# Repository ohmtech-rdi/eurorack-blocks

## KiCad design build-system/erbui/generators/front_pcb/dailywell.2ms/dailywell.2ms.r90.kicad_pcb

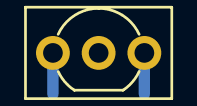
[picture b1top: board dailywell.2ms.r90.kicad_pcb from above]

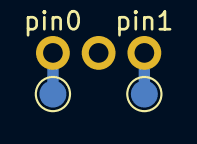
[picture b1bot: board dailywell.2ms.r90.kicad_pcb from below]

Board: 2 copper layers, 3 parts (2 on the bottom side), 2 nets.

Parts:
Pin0, Pin1: TestPoint; TestPoint_Pad_D1.5mm
ZZ1: SW_SPDT; SW_SPDT_Dailywell

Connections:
unnamed: Pin0.1, ZZ1.1
unnamed: Pin1.1, ZZ1.3

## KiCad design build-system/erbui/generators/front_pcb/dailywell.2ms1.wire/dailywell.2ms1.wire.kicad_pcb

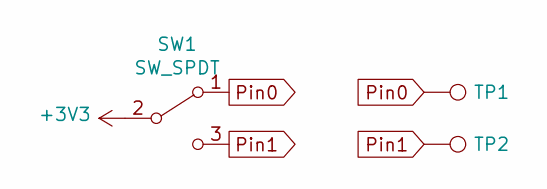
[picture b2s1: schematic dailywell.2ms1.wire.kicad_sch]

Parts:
SW1: SW_SPDT; SW_SPDT_Dailywell
TP1, TP2: TestPoint; TestPoint_Pad_D1.5mm

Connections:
+3V3: SW1.2 (B)
Pin0: SW1.1 (A), TP1.1
Pin1: SW1.3 (C), TP2.1

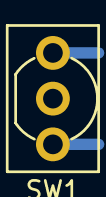
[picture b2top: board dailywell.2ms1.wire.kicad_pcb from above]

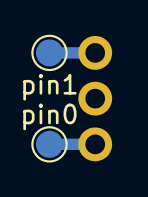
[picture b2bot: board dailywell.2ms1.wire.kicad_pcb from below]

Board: 2 copper layers, 3 parts (2 on the bottom side), 2 nets.
